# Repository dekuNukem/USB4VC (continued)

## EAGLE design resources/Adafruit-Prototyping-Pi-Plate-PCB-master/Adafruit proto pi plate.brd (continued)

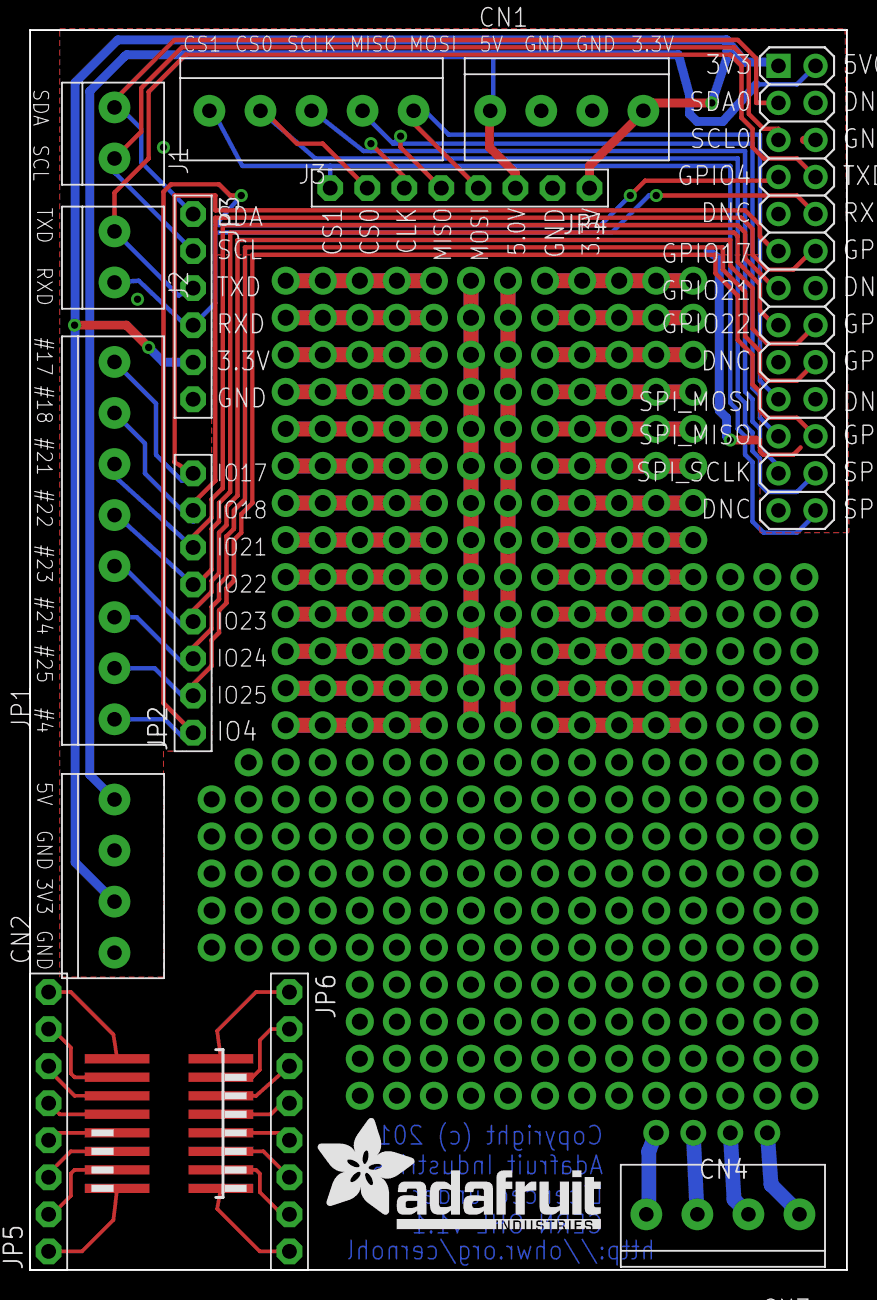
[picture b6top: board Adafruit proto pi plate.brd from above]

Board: 2 copper layers, 56.0 x 85.0 mm, 16 parts (0 on the bottom side), 40 nets.

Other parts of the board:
U$3: ADAFRUIT_TEXT_20MM

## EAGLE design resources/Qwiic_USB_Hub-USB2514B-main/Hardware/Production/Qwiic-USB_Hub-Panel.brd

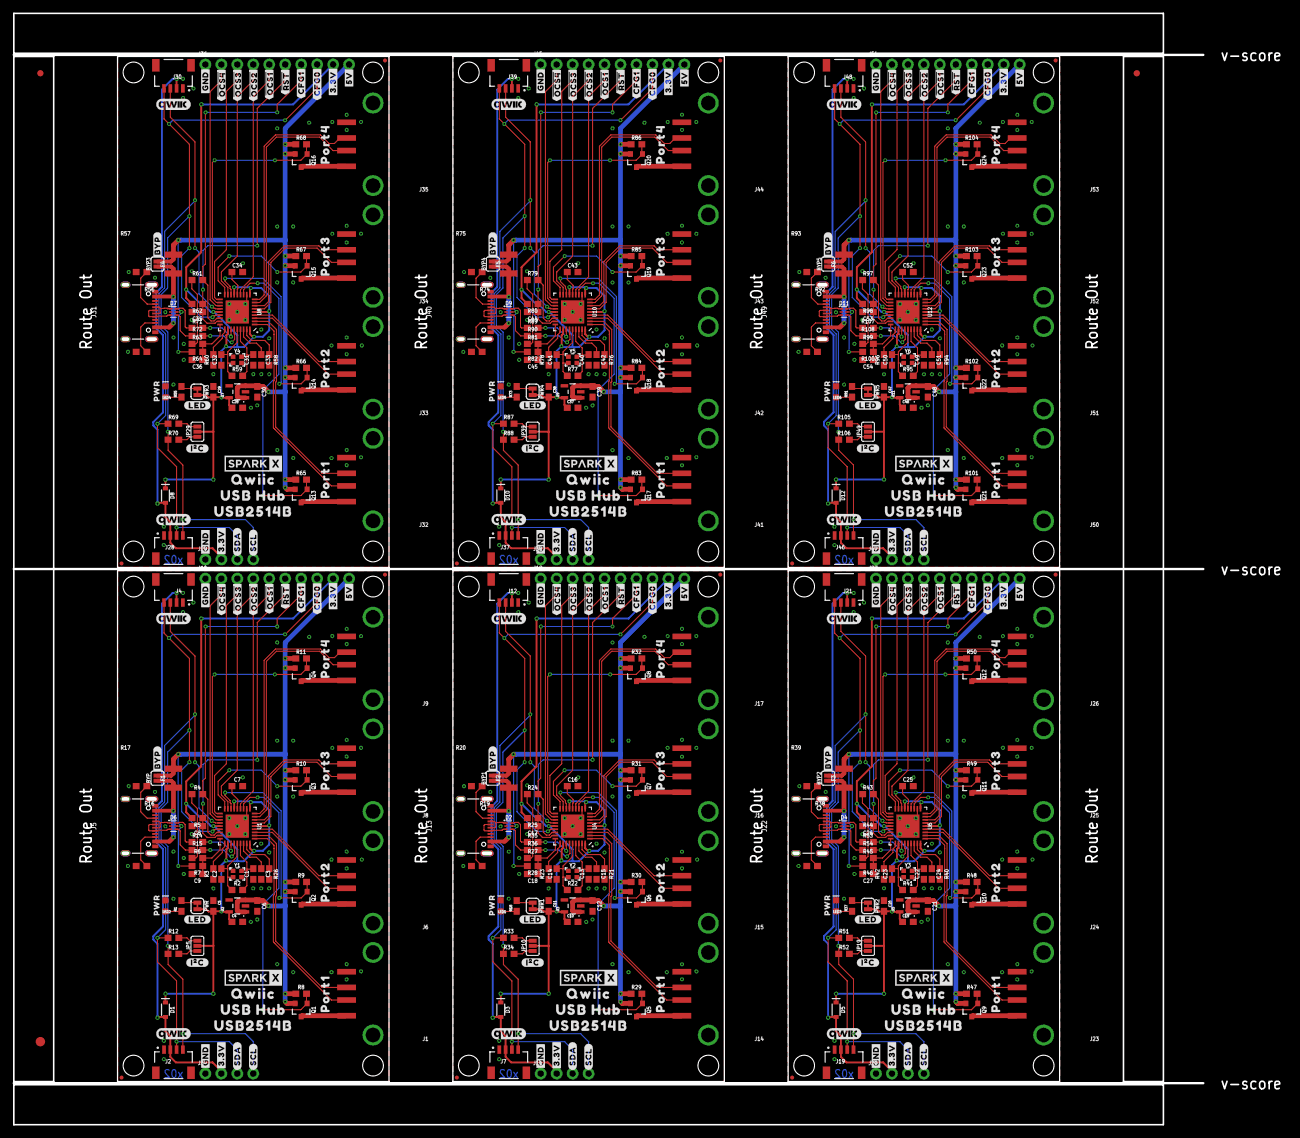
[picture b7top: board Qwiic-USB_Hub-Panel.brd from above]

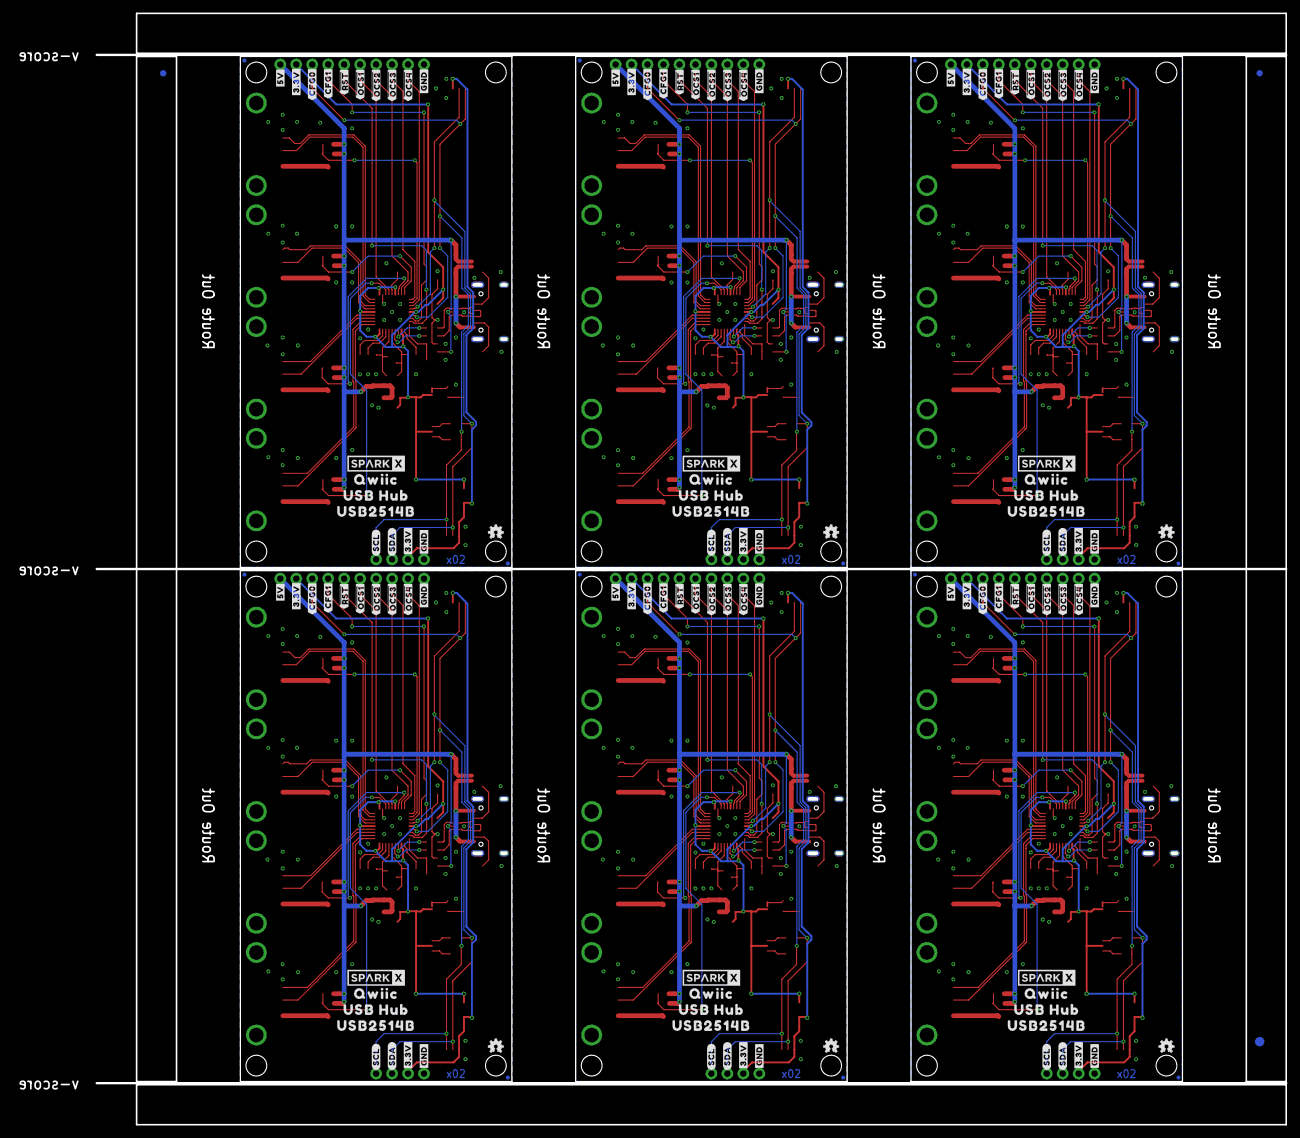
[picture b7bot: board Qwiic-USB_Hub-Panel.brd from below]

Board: 2 copper layers, 189.2 x 176.8 mm, 636 parts (129 on the bottom side), 288 nets.

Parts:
BYP, BYP1, BYP2, BYP3, BYP4, BYP5: JUMPER-SMT_2_NO_SILK; SMT-JUMPER_2_NO_SILK
C1, C2, C13, C14, C22, C23, C31, C32, C40, C41, C49, C50: 18pF; 0603
C3, C5, C7, C8, C9, C11, C15, C16, C17, C18, C20, C24, C25, C26, C27, C29, C33, C34, C35, C36, C38, C42, C43, C44, C45, C47, C51, C52, C53, C54: 0.1uF; 0603
C4, C6, C10, C12, C19, C21, C28, C30, C37, C39, C46, C48: 1.0uF; 0603
D1, D3, D5, D8, D10, D12: 3A/10V/280mV; SOD-323
D2, D4, D6, D7, D9, D11: PRTR5V0U2F; SOT886
E$1, E$2, E$3, E$4: FIDUCIAL-1X2
E$5, E$6: FIDUCIAL-1.5X3
F1, F2, F3, F4, F5, F6: 6V/2A; 1210
J1, J6, J8, J9, J14, J15, J16, J17, J23, J24, J25, J26, J32, J33, J34, J35, J41, J42, J43, J44, J50, J51, J52, J53: USB_A_FEMALE; USB-A-S-NOSILK-FEMALE
J2, J4, J7, J12, J19, J21, J28, J30, J37, J39, J46, J48: Qwiic Right Angle; JST04_1MM_RA
J3, J11, J20, J29, J38, J47: PTH; 1X04_NO_SILK
J5, J13, J22, J31, J40, J49: USB-C-16P-2LAYER-PADS
J10, J18, J27, J36, J45, J54: 1X10_NO_SILK
JP1, JP2, JP8, JP9, JP11, JP12, JP17, JP18, JP20, JP22, JP27, JP28, JP30, JP31, JP32, JP37, JP38, JP40, JP41, JP42, JP47, JP48, JP91, JP101: STAND-OFF
JP3, JP4, JP6, JP7, JP13, JP14, JP15, JP16, JP21, JP23, JP24, JP25, JP26, JP33, JP34, JP35, JP36, JP43, JP44, JP45, JP46, JP61, JP71, JP81: FIDUCIALUFIDUCIAL; MICRO-FIDUCIAL
JP5, JP10, JP19, JP29, JP39, JP49: SMT-JUMPER_3_NO_SILK
LED1, LED2, LED3, LED4, LED5, LED6: RED; LED-0603
LOGO1, LOGO3, LOGO5, LOGO7, LOGO9, LOGO11: OSHW-LOGOMINI; OSHW-LOGO-MINI
LOGO2, LOGO4, LOGO6, LOGO8, LOGO10, LOGO12: QWIIC_LOGO_CONNECTOR; QWIIC_5.5MM
PWR, PWR1, PWR2, PWR3, PWR4, PWR5: SMT-JUMPER_2_NC_TRACE_SILK
Q1, Q2, Q3, Q4, Q5, Q6, Q7, Q8, Q9, Q10, Q11, Q12, Q13, Q14, Q15, Q16, Q17, Q18, Q19, Q20, Q21, Q22, Q23, Q24: 4.3A/20V/54mΩ; SOT23-3
R1, R18, R37, R55, R73, R91: 1k; 0603
R2, R22, R41, R59, R77, R95: 1M; 0603
R3, R4, R5, R6, R7, R8, R9, R10, R11, R23, R24, R25, R27, R28, R29, R30, R31, R32, R42, R43, R44, R45, R46, R47, R48, R49, R50, R60, R61, R62, R63, R64, R65, R66, R67, R68, R78, R79, R80, R81, R82, R83, R84, R85, R86, R96, R97, R98, R99, R100, R101, R102, R103, R104: 100k; 0603
R12, R13, R33, R34, R51, R52, R69, R70, R87, R88, R105, R106: 2.2k; 0603
R14, R15, R35, R36, R53, R54, R71, R72, R89, R90, R107, R108: 22; 0603
R16, R17, R19, R20, R38, R39, R56, R57, R74, R75, R92, R93: 5.1k; 0603
R21, R26, R40, R58, R76, R94: 12k; 0603
U1, U4, U6, U8, U10, U12: USB251XB; QFN-36
U2, U3, U5, U7, U9, U11: 3.3V; SOT23-5
U$1, U$46, U$91, U$136, U$181, U$226: PORT40
U$2, U$47, U$92, U$137, U$182, U$227: PORT31
U$3, U$48, U$93, U$138, U$183, U$228: PORT22
U$4, U$49, U$94, U$139, U$184, U$229: PORT13
U$5, U$38, U$50, U$74, U$95, U$119, U$140, U$164, U$185, U$209, U$230, U$254: SPARKX-LOGO4; SPARKX-MEDIUM
U$6, U$34, U$51, U$54, U$96, U$99, U$141, U$144, U$186, U$189, U$231, U$234: #3#3V#0
U$7, U$35, U$52, U$55, U$97, U$100, U$142, U$145, U$187, U$190, U$232, U$235: #SDA#0
U$8, U$36, U$53, U$56, U$98, U$101, U$143, U$146, U$188, U$191, U$233, U$236: #SCL#0
U$9, U$33, U$57, U$58, U$102, U$103, U$147, U$148, U$192, U$193, U$237, U$238: #GND#0
U$10, U$59, U$104, U$149, U$194, U$239: #I�C#1
U$11, U$16, U$64, U$70, U$109, U$115, U$154, U$160, U$199, U$205, U$244, U$250: #GND#5
U$12, U$60, U$105, U$150, U$195, U$240: PWR0
U$13, U$31, U$61, U$71, U$106, U$116, U$151, U$161, U$196, U$206, U$241, U$251: ##RST##4
U$14, U$32, U$62, U$72, U$107, U$117, U$152, U$162, U$197, U$207, U$242, U$252: #3#3V#6
U$15, U$37, U$63, U$73, U$108, U$118, U$153, U$163, U$198, U$208, U$243, U$253: #5V#7
U$17, U$30, U$79, U$87, U$124, U$132, U$169, U$177, U$214, U$222, U$259, U$267: ##OCS1##3
U$18, U$43, U$80, U$88, U$125, U$133, U$170, U$178, U$215, U$223, U$260, U$268: ##OCS2##2
U$19, U$44, U$81, U$89, U$126, U$134, U$171, U$179, U$216, U$224, U$261, U$269: ##OCS3##1
U$20, U$45, U$82, U$90, U$127, U$135, U$172, U$180, U$217, U$225, U$262, U$270: ##OCS4##0
U$21, U$65, U$110, U$155, U$200, U$245: #BYP#0
U$22, U$39, U$67, U$75, U$112, U$120, U$157, U$165, U$202, U$210, U$247, U$255: QWIIC2
U$23, U$69, U$114, U$159, U$204, U$249: #LED#0
U$24, U$29, U$83, U$86, U$128, U$131, U$173, U$176, U$218, U$221, U$263, U$266: #CFG0#1
U$25, U$28, U$84, U$85, U$129, U$130, U$174, U$175, U$219, U$220, U$264, U$265: #CFG1#0
U$26, U$41, U$66, U$77, U$111, U$122, U$156, U$167, U$201, U$212, U$246, U$257: USB2514B0
U$27, U$40, U$68, U$76, U$113, U$121, U$158, U$166, U$203, U$211, U$248, U$256: USB_HUB1
U$42, U$78, U$123, U$168, U$213, U$258: QWIIC_5.5MM
Y1, Y2, Y3, Y4, Y5, Y6: 24MHz; CRYSTAL-SMD-2.0X1.6MM

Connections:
3.3V: C4.1, C5.2, D1.C, J10.9, JP5.2, PWR.2, R5.2, U1.5, U1.10, U1.15, U1.23, U1.29, U1.36, U2.5
3.3V1: C10.1, C11.2, D3.C, J18.9, JP10.2, PWR1.2, R25.2, U3.5, U4.5, U4.10, U4.15, U4.23, U4.29, U4.36
3.3V2: C19.1, C20.2, D5.C, J27.9, JP19.2, PWR2.2, R44.2, U5.5, U6.5, U6.10, U6.15, U6.23, U6.29, U6.36
3.3V3: C28.1, C29.2, D8.C, J36.9, JP29.2, PWR3.2, R62.2, U7.5, U8.5, U8.10, U8.15, U8.23, U8.29, U8.36
3.3V4: C37.1, C38.2, D10.C, J45.9, JP39.2, PWR4.2, R80.2, U9.5, U10.5, U10.10, U10.15, U10.23, U10.29, U10.36
3.3V5: C46.1, C47.2, D12.C, J54.9, JP49.2, PWR5.2, R98.2, U11.5, U12.5, U12.10, U12.15, U12.23, U12.29, U12.36
5V: BYP.2, C6.1, D6.5, F1.2, J10.10, Q1.2, Q2.2, Q3.2, Q4.2, R7.2, R8.1, R9.1, R10.1, R11.1, U2.1, U2.3
5V1: BYP1.2, C12.1, D2.5, F2.2, J18.10, Q5.2, Q6.2, Q7.2, Q8.2, R28.2, R29.1, R30.1, R31.1, R32.1, U3.1, U3.3
5V2: BYP2.2, C21.1, D4.5, F3.2, J27.10, Q9.2, Q10.2, Q11.2, Q12.2, R46.2, R47.1, R48.1, R49.1, R50.1, U5.1, U5.3
5V3: BYP3.2, C30.1, D7.5, F4.2, J36.10, Q13.2, Q14.2, Q15.2, Q16.2, R64.2, R65.1, R66.1, R67.1, R68.1, U7.1, U7.3
5V4: BYP4.2, C39.1, D9.5, F5.2, J45.10, Q17.2, Q18.2, Q19.2, Q20.2, R82.2, R83.1, R84.1, R85.1, R86.1, U9.1, U9.3
5V5: BYP5.2, C48.1, D11.5, F6.2, J54.10, Q21.2, Q22.2, Q23.2, Q24.2, R100.2, R101.1, R102.1, R103.1, R104.1, U11.1, U11.3
!OCS1: J10.5, U1.13
!OCS2: J10.4, U1.17
!OCS3: J10.3, U1.19
!OCS4: J10.2, U1.21
!OCS5: J18.5, U4.13
!OCS6: J18.4, U4.17
!OCS7: J18.3, U4.19
!OCS8: J18.2, U4.21
!OCS9: J27.5, U6.13
!OCS10: J27.4, U6.17
!OCS11: J27.3, U6.19
!OCS12: J27.2, U6.21
!OCS13: J36.5, U8.13
!OCS14: J36.4, U8.17
!OCS15: J36.3, U8.19
!OCS16: J36.2, U8.21
!OCS17: J45.5, U10.13
!OCS18: J45.4, U10.17
!OCS19: J45.3, U10.19
!OCS20: J45.2, U10.21
!OCS21: J54.5, U12.13
!OCS22: J54.4, U12.17
!OCS23: J54.3, U12.19
!OCS24: J54.2, U12.21
!RESET: C8.1, J10.6, R5.1, U1.26
!RESET1: C17.1, J18.6, R25.1, U4.26
!RESET2: C26.1, J27.6, R44.1, U6.26
!RESET3: C35.1, J36.6, R62.1, U8.26
!RESET4: C44.1, J45.6, R80.1, U10.26
!RESET5: C53.1, J54.6, R98.1, U12.26
CC1: J5.A5, R17.2
CC2: J5.B5, R16.2
CC3: J13.A5, R20.2
CC4: J13.B5, R19.2
CC5: J22.A5, R39.2
CC6: J22.B5, R38.2
CC7: J31.A5, R57.2
CC8: J31.B5, R56.2
CC9: J40.A5, R75.2
CC10: J40.B5, R74.2
CC11: J49.A5, R93.2
CC12: J49.B5, R92.2
CFG1: J10.7, R4.2, U1.25
CFG2: J18.7, R24.2, U4.25
CFG3: J27.7, R43.2, U6.25
CFG4: J36.7, R61.2, U8.25
CFG5: J45.7, R79.2, U10.25
CFG6: J54.7, R97.2, U12.25
D_N: D6.6, R14.1
D_N1: D2.6, R35.1
D_N2: D4.6, R53.1
D_N3: D7.6, R71.1
D_N4: D9.6, R89.1
D_N5: D11.6, R107.1
D_P: D6.4, R15.1
D_P1: D2.4, R36.1
D_P2: D4.4, R54.1
D_P3: D7.4, R72.1
D_P4: D9.4, R90.1
D_P5: D11.4, R108.1
GND: C1.1, C2.1, C3.2, C4.2, C5.1, C6.2, C7.2, C8.2, C9.2, D6.2, J1.GND, J2.1, J3.1, J4.1, J5.GND, J5.GND2, J5.SHLD1, J5.SHLD2, J5.SHLD3, J5.SHLD4, J6.GND, J8.GND, J9.GND, J10.1, LED2.C, R3.1, R4.1, R6.1, R16.1, R17.1, R26.2, U1.11, U1.EP, U2.2
GND1: C10.2, C11.1, C12.2, C13.1, C14.1, C15.2, C16.2, C17.2, C18.2, D2.2, J7.1, J11.1, J12.1, J13.GND, J13.GND2, J13.SHLD1, J13.SHLD2, J13.SHLD3, J13.SHLD4, J14.GND, J15.GND, J16.GND, J17.GND, J18.1, LED1.C, R19.1, R20.1, R21.2, R23.1, R24.1, R27.1, U3.2, U4.11, U4.EP
GND2: C19.2, C20.1, C21.2, C22.1, C23.1, C24.2, C25.2, C26.2, C27.2, D4.2, J19.1, J20.1, J21.1, J22.GND, J22.GND2, J22.SHLD1, J22.SHLD2, J22.SHLD3, J22.SHLD4, J23.GND, J24.GND, J25.GND, J26.GND, J27.1, LED3.C, R38.1, R39.1, R40.2, R42.1, R43.1, R45.1, U5.2, U6.11, U6.EP
GND3: C28.2, C29.1, C30.2, C31.1, C32.1, C33.2, C34.2, C35.2, C36.2, D7.2, J28.1, J29.1, J30.1, J31.GND, J31.GND2, J31.SHLD1, J31.SHLD2, J31.SHLD3, J31.SHLD4, J32.GND, J33.GND, J34.GND, J35.GND, J36.1, LED4.C, R56.1, R57.1, R58.2, R60.1, R61.1, R63.1, U7.2, U8.11, U8.EP
GND4: C37.2, C38.1, C39.2, C40.1, C41.1, C42.2, C43.2, C44.2, C45.2, D9.2, J37.1, J38.1, J39.1, J40.GND, J40.GND2, J40.SHLD1, J40.SHLD2, J40.SHLD3, J40.SHLD4, J41.GND, J42.GND, J43.GND, J44.GND, J45.1, LED5.C, R74.1, R75.1, R76.2, R78.1, R79.1, R81.1, U9.2, U10.11, U10.EP
GND5: C46.2, C47.1, C48.2, C49.1, C50.1, C51.2, C52.2, C53.2, C54.2, D11.2, J46.1, J47.1, J48.1, J49.GND, J49.GND2, J49.SHLD1, J49.SHLD2, J49.SHLD3, J49.SHLD4, J50.GND, J51.GND, J52.GND, J53.GND, J54.1, LED6.C, R92.1, R93.1, R94.2, R96.1, R97.1, R99.1, U11.2, U12.11, U12.EP
unnamed: J1.VBUS, Q1.3
unnamed: J6.VBUS, Q2.3
unnamed: J8.VBUS, Q3.3
unnamed: J9.VBUS, Q4.3
unnamed: R26.1, U1.35
unnamed: C1.2, R2.2, U1.33, Y1.3
unnamed: BYP.1, F1.1, J5.VBUS1, J5.VBUS2
unnamed: C2.2, R2.1, U1.32, Y1.1
unnamed: JP5.1, R13.2
unnamed: LED2.A, R1.1
unnamed: R3.2, U1.28
unnamed: LED1.A, R18.1
unnamed: C3.1, U1.34
unnamed: C7.1, U1.14
unnamed: JP5.3, R12.2
unnamed: R14.2, U1.30
unnamed: PWR.1, R1.2
unnamed: R15.2, U1.31
unnamed: PWR1.1, R18.2
unnamed: C13.2, R22.2, U4.33, Y2.3
unnamed: D1.A, J2.2, J3.2, J4.2
unnamed: C14.2, R22.1, U4.32, Y2.1
unnamed: R21.1, U4.35
unnamed: R23.2, U4.28
unnamed: C15.1, U4.34
unnamed: C16.1, U4.14
unnamed: J14.VBUS, Q5.3
unnamed: J15.VBUS, Q6.3
unnamed: J16.VBUS, Q7.3
unnamed: J17.VBUS, Q8.3
unnamed: BYP1.1, F2.1, J13.VBUS1, J13.VBUS2
unnamed: JP10.1, R34.2
unnamed: JP10.3, R33.2
unnamed: R35.2, U4.30
unnamed: R36.2, U4.31
unnamed: D3.A, J7.2, J11.2, J12.2
unnamed: LED3.A, R37.1
unnamed: PWR2.1, R37.2
unnamed: C22.2, R41.2, U6.33, Y3.3
unnamed: C23.2, R41.1, U6.32, Y3.1
unnamed: R40.1, U6.35
unnamed: R42.2, U6.28
unnamed: C24.1, U6.34
unnamed: C25.1, U6.14
unnamed: J23.VBUS, Q9.3
unnamed: J24.VBUS, Q10.3
unnamed: J25.VBUS, Q11.3
unnamed: J26.VBUS, Q12.3
unnamed: BYP2.1, F3.1, J22.VBUS1, J22.VBUS2
unnamed: JP19.1, R52.2
unnamed: JP19.3, R51.2
unnamed: R53.2, U6.30
unnamed: R54.2, U6.31
unnamed: D5.A, J19.2, J20.2, J21.2
unnamed: LED4.A, R55.1
unnamed: PWR3.1, R55.2
unnamed: C31.2, R59.2, U8.33, Y4.3
unnamed: C32.2, R59.1, U8.32, Y4.1
unnamed: R58.1, U8.35
unnamed: R60.2, U8.28
unnamed: C33.1, U8.34
unnamed: C34.1, U8.14
unnamed: J32.VBUS, Q13.3
unnamed: J33.VBUS, Q14.3
unnamed: J34.VBUS, Q15.3
unnamed: J35.VBUS, Q16.3
unnamed: BYP3.1, F4.1, J31.VBUS1, J31.VBUS2
unnamed: JP29.1, R70.2
unnamed: JP29.3, R69.2
unnamed: R71.2, U8.30
unnamed: R72.2, U8.31
unnamed: D8.A, J28.2, J29.2, J30.2
unnamed: LED5.A, R73.1
unnamed: PWR4.1, R73.2
unnamed: C40.2, R77.2, U10.33, Y5.3
unnamed: C41.2, R77.1, U10.32, Y5.1
unnamed: R76.1, U10.35
unnamed: R78.2, U10.28
unnamed: C42.1, U10.34
unnamed: C43.1, U10.14
unnamed: J41.VBUS, Q17.3
unnamed: J42.VBUS, Q18.3
unnamed: J43.VBUS, Q19.3
unnamed: J44.VBUS, Q20.3
unnamed: BYP4.1, F5.1, J40.VBUS1, J40.VBUS2
unnamed: JP39.1, R88.2
unnamed: JP39.3, R87.2
unnamed: R89.2, U10.30
unnamed: R90.2, U10.31
unnamed: D10.A, J37.2, J38.2, J39.2
unnamed: LED6.A, R91.1
unnamed: PWR5.1, R91.2
unnamed: C49.2, R95.2, U12.33, Y6.3
unnamed: C50.2, R95.1, U12.32, Y6.1
unnamed: R94.1, U12.35
unnamed: R96.2, U12.28
unnamed: C51.1, U12.34
unnamed: C52.1, U12.14
unnamed: J50.VBUS, Q21.3
unnamed: J51.VBUS, Q22.3
unnamed: J52.VBUS, Q23.3
unnamed: J53.VBUS, Q24.3
unnamed: BYP5.1, F6.1, J49.VBUS1, J49.VBUS2
unnamed: JP49.1, R106.2
unnamed: JP49.3, R105.2
unnamed: R107.2, U12.30
unnamed: R108.2, U12.31
unnamed: D12.A, J46.2, J47.2, J48.2
PORT1_N: J1.D-, U1.1
PORT1_N1: J14.D-, U4.1
PORT1_N2: J23.D-, U6.1
PORT1_N3: J32.D-, U8.1
PORT1_N4: J41.D-, U10.1
PORT1_N5: J50.D-, U12.1
PORT1_P: J1.D+, U1.2
PORT1_P1: J14.D+, U4.2
PORT1_P2: J23.D+, U6.2
PORT1_P3: J32.D+, U8.2
PORT1_P4: J41.D+, U10.2
PORT1_P5: J50.D+, U12.2
PORT2_N: J6.D-, U1.3
PORT2_N1: J15.D-, U4.3
PORT2_N2: J24.D-, U6.3
PORT2_N3: J33.D-, U8.3
PORT2_N4: J42.D-, U10.3
PORT2_N5: J51.D-, U12.3
PORT2_P: J6.D+, U1.4
PORT2_P1: J15.D+, U4.4
PORT2_P2: J24.D+, U6.4
PORT2_P3: J33.D+, U8.4
PORT2_P4: J42.D+, U10.4
PORT2_P5: J51.D+, U12.4
PORT3_N: J8.D-, U1.6
PORT3_N1: J16.D-, U4.6
PORT3_N2: J25.D-, U6.6
PORT3_N3: J34.D-, U8.6
PORT3_N4: J43.D-, U10.6
PORT3_N5: J52.D-, U12.6
PORT3_P: J8.D+, U1.7
PORT3_P1: J16.D+, U4.7
PORT3_P2: J25.D+, U6.7
PORT3_P3: J34.D+, U8.7
PORT3_P4: J43.D+, U10.7
PORT3_P5: J52.D+, U12.7
PORT4_N: J9.D-, U1.8
PORT4_N1: J17.D-, U4.8
PORT4_N2: J26.D-, U6.8
PORT4_N3: J35.D-, U8.8
PORT4_N4: J44.D-, U10.8
PORT4_N5: J53.D-, U12.8
PORT4_P: J9.D+, U1.9
PORT4_P1: J17.D+, U4.9
PORT4_P2: J26.D+, U6.9
PORT4_P3: J35.D+, U8.9
PORT4_P4: J44.D+, U10.9
PORT4_P5: J53.D+, U12.9
PRTPWR1: Q1.1, R8.2, U1.12
PRTPWR2: Q2.1, R9.2, U1.16
PRTPWR3: Q3.1, R10.2, U1.18
PRTPWR4: Q4.1, R11.2, U1.20
PRTPWR5: Q5.1, R29.2, U4.12
PRTPWR6: Q6.1, R30.2, U4.16
PRTPWR7: Q7.1, R31.2, U4.18
PRTPWR8: Q8.1, R32.2, U4.20
PRTPWR9: Q9.1, R47.2, U6.12
PRTPWR10: Q10.1, R48.2, U6.16
PRTPWR11: Q11.1, R49.2, U6.18
PRTPWR12: Q12.1, R50.2, U6.20
PRTPWR13: Q13.1, R65.2, U8.12
PRTPWR14: Q14.1, R66.2, U8.16
PRTPWR15: Q15.1, R67.2, U8.18
PRTPWR16: Q16.1, R68.2, U8.20
PRTPWR17: Q17.1, R83.2, U10.12
PRTPWR18: Q18.1, R84.2, U10.16
PRTPWR19: Q19.1, R85.2, U10.18
PRTPWR20: Q20.1, R86.2, U10.20
PRTPWR21: Q21.1, R101.2, U12.12
PRTPWR22: Q22.1, R102.2, U12.16
PRTPWR23: Q23.1, R103.2, U12.18
PRTPWR24: Q24.1, R104.2, U12.20
SCL/CFG0: J2.4, J3.4, J4.4, J10.8, R13.1, U1.24
SCL/CFG1: J7.4, J11.4, J12.4, J18.8, R34.1, U4.24
SCL/CFG2: J19.4, J20.4, J21.4, J27.8, R52.1, U6.24
SCL/CFG3: J28.4, J29.4, J30.4, J36.8, R70.1, U8.24
SCL/CFG4: J37.4, J38.4, J39.4, J45.8, R88.1, U10.24
SCL/CFG5: J46.4, J47.4, J48.4, J54.8, R106.1, U12.24
SDA: J2.3, J3.3, J4.3, R12.1, U1.22
SDA1: J7.3, J11.3, J12.3, R33.1, U4.22
SDA2: J19.3, J20.3, J21.3, R51.1, U6.22
SDA3: J28.3, J29.3, J30.3, R69.1, U8.22
SDA4: J37.3, J38.3, J39.3, R87.1, U10.22
SDA5: J46.3, J47.3, J48.3, R105.1, U12.22
UNP_D+: D6.3, J5.A6, J5.B6
UNP_D+1: D2.3, J13.A6, J13.B6
UNP_D+2: D4.3, J22.A6, J22.B6
UNP_D+3: D7.3, J31.A6, J31.B6
UNP_D+4: D9.3, J40.A6, J40.B6
UNP_D+5: D11.3, J49.A6, J49.B6
UNP_D-: D6.1, J5.A7, J5.B7
UNP_D-1: D2.1, J13.A7, J13.B7
UNP_D-2: D4.1, J22.A7, J22.B7
UNP_D-3: D7.1, J31.A7, J31.B7
UNP_D-4: D9.1, J40.A7, J40.B7
UNP_D-5: D11.1, J49.A7, J49.B7
VBUS_DET: C9.1, R6.2, R7.1, U1.27
VBUS_DET1: C18.1, R27.2, R28.1, U4.27
VBUS_DET2: C27.1, R45.2, R46.1, U6.27
VBUS_DET3: C36.1, R63.2, R64.1, U8.27
VBUS_DET4: C45.1, R81.2, R82.1, U10.27
VBUS_DET5: C54.1, R99.2, R100.1, U12.27
